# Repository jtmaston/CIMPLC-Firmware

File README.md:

<div style="text-align: justify">

# CIMPLC 
The CIMPLC is a low-cost, open source high pin-count programmable logic controller, designed as a project while studying at the University of Politehnica, Bucharest. It is designed as a replacement for the aging hardware found inside the CIM ( Computer Integrated Manufacturing ) workcell located in our faculty.

# The software
The firmware is based on FreeRTOS, offering vast functionality. The stand-out feature of this design is the implementation of the concept of vPLC, or virtual PLC. It also implements a fast optimizing compiler to translate IEC 61131-3 instructions to bytecode which can be loaded faster from EEPROM.

Fast, predictible code execution is the goal of every system, and the CIMPLC is no exception. The end-goal of the code is to be implemented according to the most rigorous standards. In its final version, code will be written following the MISRA standard.
## Features [WIP]

### WiFi programmability and monitoring
The software allows both firmware updates over the air (OTA), as well as binary uploads for the PLC.

Furthermore, the status of the PLC can be monitored at any time by the use of a web interface. Pin status, direction, and code execution can be accessed, as well as whatever logs may be produced by the code.

### vPLC
vPLC, short for Virtual PLC, simplifies the concept of a PLC to its simplest form: a finite state machine. This allows for the creation of multiple threads of execution, each with access to I/Os and interfaces, while having distinct memory spaces, program stacks and counters. This allows for higher flexibility of the system.

### WASM
## Limitations

???
## Contributors

Mihai Costin, for the WASM magic [@mihaicostin34](https://github.com/mihaicostin34)
## License

This project is licensed under [GNU AGPLv3](https://choosealicense.com/licenses/agpl-3.0/).
</div>

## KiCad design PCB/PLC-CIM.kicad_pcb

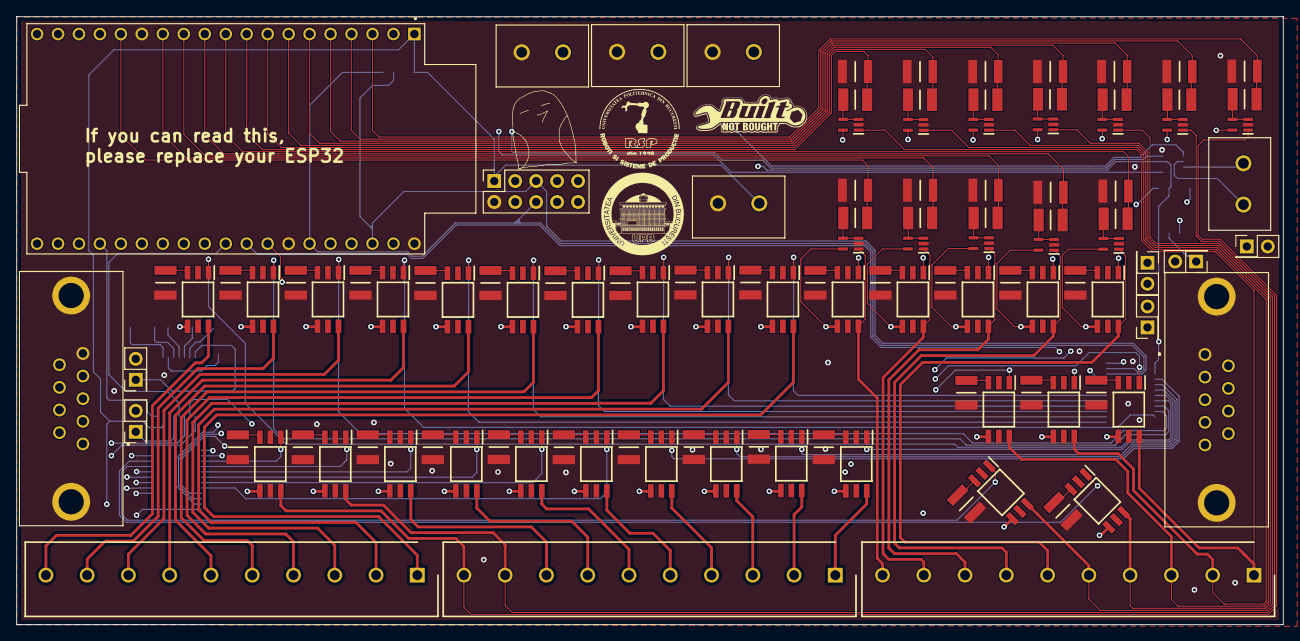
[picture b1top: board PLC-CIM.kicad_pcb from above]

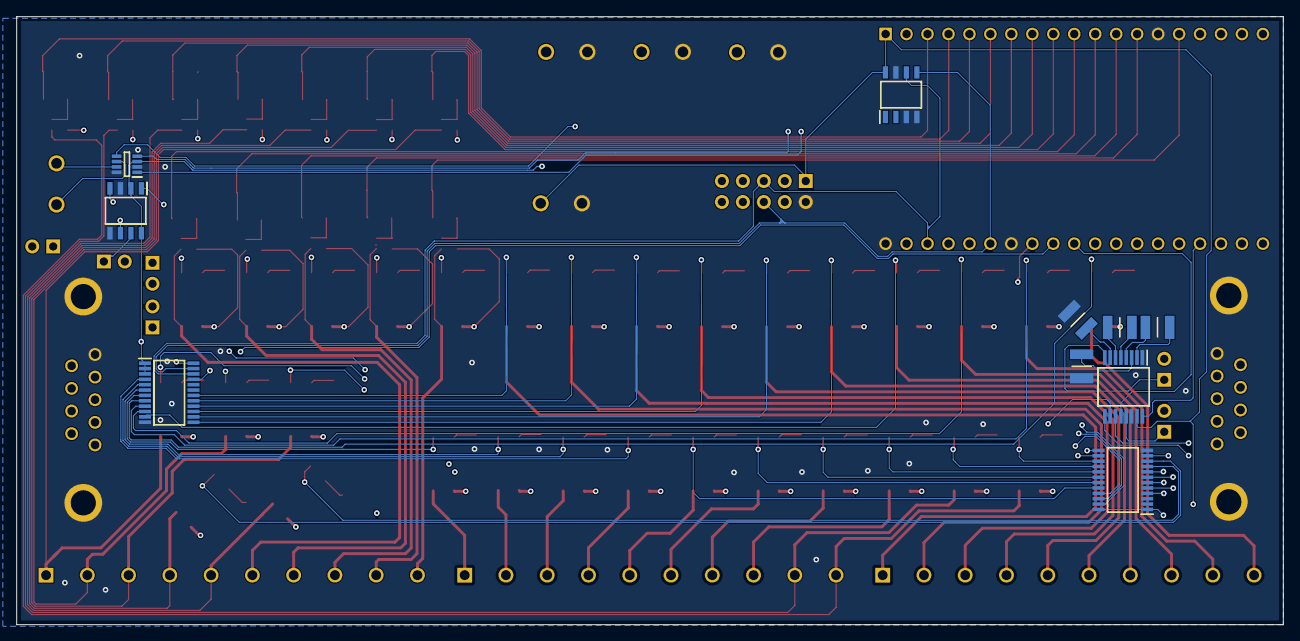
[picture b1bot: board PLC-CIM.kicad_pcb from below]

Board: 4 copper layers, 153.5 x 73.7 mm, 124 parts (10 on the bottom side), 149 nets.

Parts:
C1, C2, C3, C4: 12103C104KAT2A; CAPC3325X94N
IC1, IC2, IC3, IC4, IC5, IC6, IC13, IC14, IC15, IC16, IC17, IC18, IC25, IC26, IC27, IC28, IC29, IC30, IC32, IC33, IC34, IC35, IC36, IC37, IC38, IC39, IC40, IC41, IC42, IC43: TLP172AM_TPR,E; SOIC127P700X230-6N
IC7, IC8, IC9, IC10, IC11, IC12, IC19, IC20, IC21, IC22, IC23, IC24: TLV9351IDCKR; SOT65P210X110-5N
IC31: MAX3221IDBRE4; SOP65P780X200-16N
IC44, IC46: PCA9555PW,118; SOP65P640X110-24N
IC45: TCAN337DCNR; SOT65P280X145-8N
IC47: SN65HVD75DR; SOIC127P600X175-8N
J1, J2, J3: TB001-500-10BE; SHDR10W100P0X500_1X10_5000X900X1250P
J4, J5, J6, J7, J12: TC0203620000G
J8, J13: 750678-1; 7506781
J9, J10, J14, J15, J16, J17: Conn_02x01; PinHeader_2x01_P2.54mm_Vertical
J11: Conn_02x05_Odd_Even; PinSocket_2x05_P2.54mm_Vertical
R1, R2, R3, R4, R5, R6, R19, R20, R21, R22, R23, R24, R37, R38, R39, R40, R41, R42, R43, R44, R45, R46, R47, R48, R49, R50, R51, R52, R53, R54: CRCW1210267RFKEA; RESC3225X60N
R7, R8, R9, R10, R11, R12, R25, R26, R27, R28, R29, R30: RK73B2ETTD152J; RESC3226X70N
R13, R14, R15, R16, R17, R18, R31, R32, R33, R34, R35, R36: RMCF1210FT10K0; RESC3225X70N
U1: ESP32-DEVKITC; MODULE_ESP32-DEVKITC
U2: AT24CM02-SSHM-B; SOIC127P600X175-8N

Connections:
+3.3V: IC31.15 (VCC), IC44.1 (~INT), IC44.2 (A1), IC44.3 (A2), IC44.24 (VDD), IC45.3 (VCC), IC46.1 (~INT), IC46.2 (A1), IC46.3 (A2), IC46.24 (VDD), IC47.2 (~RE), IC47.8 (VCC), J5.1, J11.1, U1.1 (3V3), U2.8 (VCC)
+24V: IC1.4 (DRAIN_1), IC2.4 (DRAIN_1), IC3.4 (DRAIN_1), IC4.4 (DRAIN_1), IC5.4 (DRAIN_1), IC6.4 (DRAIN_1), IC7.5 (V+), IC8.5 (V+), IC9.5 (V+), IC10.5 (V+), IC11.5 (V+), IC12.5 (V+), IC13.4 (DRAIN_1), IC14.4 (DRAIN_1), IC15.4 (DRAIN_1), IC16.4 (DRAIN_1), IC17.4 (DRAIN_1), IC18.4 (DRAIN_1), IC19.5 (V+), IC20.5 (V+), IC21.5 (V+), IC22.5 (V+), IC23.5 (V+), IC24.5 (V+), IC25.4 (DRAIN_1), IC26.4 (DRAIN_1), IC27.4 (DRAIN_1), IC28.4 (DRAIN_1), IC29.4 (DRAIN_1), IC30.4 (DRAIN_1), IC32.4 (DRAIN_1), IC33.4 (DRAIN_1), IC34.4 (DRAIN_1), IC35.4 (DRAIN_1), IC36.4 (DRAIN_1), IC37.4 (DRAIN_1), IC38.4 (DRAIN_1), IC39.4 (DRAIN_1), IC40.4 (DRAIN_1), IC41.4 (DRAIN_1), IC42.4 (DRAIN_1), IC43.4 (DRAIN_1), J4.1, J6.1, J7.1, J17.2
/O Block 1/O_ACT_1: IC6.1 (ANODE), IC44.4 (I/O0_0)
/O Block 1/O_ACT_2: IC5.1 (ANODE), IC44.5 (I/O0_1)
/O Block 1/O_ACT_3: IC4.1 (ANODE), IC44.6 (I/O0_2)
/O Block 1/O_ACT_4: IC3.1 (ANODE), IC44.7 (I/O0_3)
/O Block 1/O_ACT_5: IC2.1 (ANODE), IC44.8 (I/O0_4)
/O Block 1/O_ACT_6: IC1.1 (ANODE), IC44.9 (I/O0_5)
/O Block 2/O_ACT_1: IC18.1 (ANODE), IC44.10 (I/O0_6)
/O Block 2/O_ACT_2: IC17.1 (ANODE), IC44.11 (I/O0_7)
/O Block 2/O_ACT_3: IC16.1 (ANODE), IC44.13 (I/O1_0)
/O Block 2/O_ACT_4: IC15.1 (ANODE), IC44.14 (I/O1_1)
/O Block 2/O_ACT_5: IC14.1 (ANODE), IC44.15 (I/O1_2)
/O Block 2/O_ACT_6: IC13.1 (ANODE), IC44.16 (I/O1_3)
/O Block 3/O_ACT_1: IC30.1 (ANODE), IC44.17 (I/O1_4)
/O Block 3/O_ACT_2: IC29.1 (ANODE), IC44.18 (I/O1_5)
/O Block 3/O_ACT_3: IC28.1 (ANODE), IC44.19 (I/O1_6)
/O Block 3/O_ACT_4: IC27.1 (ANODE), IC44.20 (I/O1_7)
/O Block 3/O_ACT_5: IC26.1 (ANODE), IC46.4 (I/O0_0)
/O Block 3/O_ACT_6: IC25.1 (ANODE), IC46.5 (I/O0_1)
/O Block 4/O_ACT_1: IC37.1 (ANODE), IC46.6 (I/O0_2)
/O Block 4/O_ACT_2: IC36.1 (ANODE), IC46.7 (I/O0_3)
/O Block 4/O_ACT_3: IC35.1 (ANODE), IC46.8 (I/O0_4)
/O Block 4/O_ACT_4: IC34.1 (ANODE), IC46.9 (I/O0_5)
/O Block 4/O_ACT_5: IC33.1 (ANODE), IC46.10 (I/O0_6)
/O Block 4/O_ACT_6: IC32.1 (ANODE), IC46.11 (I/O0_7)
/O Block 5/O_ACT_1: IC43.1 (ANODE), IC46.13 (I/O1_0)
/O Block 5/O_ACT_2: IC42.1 (ANODE), IC46.14 (I/O1_1)
/O Block 5/O_ACT_3: IC41.1 (ANODE), IC46.15 (I/O1_2)
/O Block 5/O_ACT_4: IC40.1 (ANODE), IC46.16 (I/O1_3)
/O Block 5/O_ACT_5: IC39.1 (ANODE), IC46.17 (I/O1_4)
/O Block 5/O_ACT_6: IC38.1 (ANODE), IC46.18 (I/O1_5)
ADR_1: IC44.21 (A0), U1.31 (IO19)
ADR_2: IC46.21 (A0), U1.30 (IO18)
CAN_FAULT: IC45.5 (FAULT), U1.26 (IO4)
CAN_RX: IC45.1 (TXD), U1.24 (IO2)
CAN_TX: IC45.4 (RXD), U1.25 (IO0)
FORCEOFF: IC31.12 (FORCEON), U1.29 (IO5)
FORCEON: IC31.16 (~FORCEOFF), U1.23 (IO15)
GND: C3.1, C4.2, IC7.2 (V-), IC8.2 (V-), IC9.2 (V-), IC10.2 (V-), IC11.2 (V-), IC12.2 (V-), IC19.2 (V-), IC20.2 (V-), IC21.2 (V-), IC22.2 (V-), IC23.2 (V-), IC24.2 (V-), IC31.1 (~EN), IC31.14 (GND), IC44.12 (VSS), IC45.2 (GND), IC45.8 (S), IC46.12 (VSS), IC47.3 (DE), IC47.5 (GND), J4.2, J5.2, J6.2, J7.2, J8.5, J8.MH1, J8.MH2, J11.2, J13.1, J13.MH1, J13.MH2, R1.2, R2.2, R3.2, R4.2, R5.2, R6.2, R7.2, R8.2, R9.2, R10.2, R11.2, R12.2, R19.2, R20.2, R21.2, R22.2, R23.2, R24.2, R25.2, R26.2, R27.2, R28.2, R29.2, R30.2, R37.2, R38.2, R39.2, R40.2, R41.2, R42.2, R43.2, R44.2, R45.2, R46.2, R47.2, R48.2, R49.2, R50.2, R51.2, R52.2, R53.2, R54.2, U1.14 (GND1), U1.32 (GND2), U1.38 (GND3), U2.3 (A2), U2.4 (GND), U2.7 (WP)
GPIO_1: IC6.6 (DRAIN_2), IC8.1 (IN+), J1.10
GPIO_2: IC5.6 (DRAIN_2), IC7.1 (IN+), J1.9
GPIO_3: IC4.6 (DRAIN_2), IC12.1 (IN+), J1.8
GPIO_4: IC3.6 (DRAIN_2), IC11.1 (IN+), J1.7
GPIO_5: IC2.6 (DRAIN_2), IC10.1 (IN+), J1.6
GPIO_6: IC1.6 (DRAIN_2), IC9.1 (IN+), J1.5
GPIO_7: IC18.6 (DRAIN_2), IC20.1 (IN+), J1.4
GPIO_8: IC17.6 (DRAIN_2), IC19.1 (IN+), J1.3
GPIO_9: IC16.6 (DRAIN_2), IC24.1 (IN+), J1.2
GPIO_10: IC15.6 (DRAIN_2), IC23.1 (IN+), J1.1
GPIO_11: IC14.6 (DRAIN_2), IC22.1 (IN+), J2.10
GPIO_12: IC13.6 (DRAIN_2), IC21.1 (IN+), J2.9
MCU_IN_1: R27.1, R33.2, U1.4 (SENSOR_VN)
MCU_IN_2: R28.1, R34.2, U1.3 (SENSOR_VP)
MCU_IN_3: R29.1, R35.2, U1.9 (IO25)
MCU_IN_4: R30.1, R36.2, U1.8 (IO33)
MCU_IN_5: R25.1, R31.2, U1.7 (IO32)
MCU_IN_6: R26.1, R32.2, U1.6 (IO35)
MCU_IN_7: R9.1, R15.2, U1.5 (IO34)
MCU_IN_8: R10.1, R16.2, U1.10 (IO26)
MCU_IN_9: R11.1, R17.2, U1.11 (IO27)
MCU_IN_10: R12.1, R18.2, U1.12 (IO14)
MCU_IN_11: R7.1, R13.2, U1.13 (IO12)
MCU_IN_12: R8.1, R14.2, U1.15 (IO13)
unnamed: IC1.3 (CATHODE), R1.1
unnamed: IC2.3 (CATHODE), R2.1
unnamed: IC3.3 (CATHODE), R3.1
unnamed: IC4.3 (CATHODE), R4.1
unnamed: IC5.3 (CATHODE), R5.1
unnamed: IC6.3 (CATHODE), R6.1
unnamed: IC7.3 (IN-), IC7.4 (OUT), R13.1
unnamed: IC8.3 (IN-), IC8.4 (OUT), R14.1
unnamed: IC9.3 (IN-), IC9.4 (OUT), R15.1
unnamed: IC10.3 (IN-), IC10.4 (OUT), R16.1
unnamed: IC11.3 (IN-), IC11.4 (OUT), R17.1
unnamed: IC12.3 (IN-), IC12.4 (OUT), R18.1
unnamed: IC13.3 (CATHODE), R19.1
unnamed: IC14.3 (CATHODE), R20.1
unnamed: IC15.3 (CATHODE), R21.1
unnamed: IC16.3 (CATHODE), R22.1
unnamed: IC17.3 (CATHODE), R23.1
unnamed: IC18.3 (CATHODE), R24.1
unnamed: IC19.3 (IN-), IC19.4 (OUT), R31.1
unnamed: IC20.3 (IN-), IC20.4 (OUT), R32.1
unnamed: IC21.3 (IN-), IC21.4 (OUT), R33.1
unnamed: IC22.3 (IN-), IC22.4 (OUT), R34.1
unnamed: IC23.3 (IN-), IC23.4 (OUT), R35.1
unnamed: IC24.3 (IN-), IC24.4 (OUT), R36.1
unnamed: IC25.3 (CATHODE), R37.1
unnamed: IC26.3 (CATHODE), R38.1
unnamed: IC27.3 (CATHODE), R39.1
unnamed: IC28.3 (CATHODE), R40.1
unnamed: IC29.3 (CATHODE), R41.1
unnamed: IC30.3 (CATHODE), R42.1
unnamed: C1.2, IC31.2 (C1+)
unnamed: C1.1, IC31.4 (C1-)
unnamed: C2.2, IC31.5 (C2+)
unnamed: C2.1, IC31.6 (C2-)
unnamed: IC31.13 (DOUT), J9.1
unnamed: IC31.8 (RIN), J10.1
unnamed: C3.2, IC31.3 (V+)
unnamed: C4.1, IC31.7 (V-)
unnamed: IC32.3 (CATHODE), R43.1
unnamed: IC33.3 (CATHODE), R44.1
unnamed: IC34.3 (CATHODE), R45.1
unnamed: IC35.3 (CATHODE), R46.1
unnamed: IC36.3 (CATHODE), R47.1
unnamed: IC37.3 (CATHODE), R48.1
unnamed: IC38.3 (CATHODE), R49.1
unnamed: IC39.3 (CATHODE), R50.1
unnamed: IC40.3 (CATHODE), R51.1
unnamed: IC41.3 (CATHODE), R52.1
unnamed: IC42.3 (CATHODE), R53.1
unnamed: IC43.3 (CATHODE), R54.1
unnamed: IC45.7 (CANH), J12.2
unnamed: IC45.6 (CANL), J12.1
unnamed: IC47.6 (A), J15.1
unnamed: IC47.7 (B), J14.1
unnamed: J8.2, J9.2
unnamed: J8.3, J10.2
unnamed: J13.3, J14.2
unnamed: J13.8, J15.2
unnamed: J13.6, J16.1
unnamed: J13.7, J17.1
OUT_13: IC30.6 (DRAIN_2), J2.8
OUT_14: IC29.6 (DRAIN_2), J2.7
OUT_15: IC28.6 (DRAIN_2), J2.6
OUT_16: IC27.6 (DRAIN_2), J2.5
OUT_17: IC26.6 (DRAIN_2), J2.4
OUT_18: IC25.6 (DRAIN_2), J2.3
OUT_19: IC37.6 (DRAIN_2), J2.2
OUT_20: IC36.6 (DRAIN_2), J2.1
OUT_21: IC35.6 (DRAIN_2), J3.10
OUT_22: IC34.6 (DRAIN_2), J3.9
OUT_23: IC33.6 (DRAIN_2), J3.8
OUT_24: IC32.6 (DRAIN_2), J3.7
OUT_25: IC43.6 (DRAIN_2), J3.6
OUT_26: IC42.6 (DRAIN_2), J3.5
OUT_27: IC41.6 (DRAIN_2), J3.4
OUT_28: IC40.6 (DRAIN_2), J3.3
OUT_29: IC39.6 (DRAIN_2), J3.2
OUT_30: IC38.6 (DRAIN_2), J3.1
RS232_STATUS: IC31.10 (~INVALID), U1.37 (IO23)
RX0: IC31.9 (ROUT), U1.34 (RXD0)
RX1: IC47.1 (R), U1.27 (IO16)
SCL: IC44.22 (SCL), IC46.22 (SCL), J11.5, U1.36 (IO22), U2.6 (SCL)
SDA: IC44.23 (SDA), IC46.23 (SDA), J11.6, U1.33 (IO21), U2.5 (SDA)
TX0: IC31.11 (DIN), U1.35 (TXD0)
TX1: IC47.4 (D), U1.28 (IO17)

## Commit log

2023-04-22 Remove some garbage
2023-04-22 # Title: Summary, imperative, start upper case, don't end with a period # No more than 50 chars. #### 50 chars is here: # Prepping repo
    # Remember blank line between title and body.
    # Body: Explain *what* and *why* (not *how*). Include task ID (Jira issue).
    # Wrap at 72 chars. ################################## which is here: #
    Deleted lib files that did not belong to KiCAD
    Altered project paths to be referenced to local project, ensuring portability
    # At the end: Include Co-authored-by for all contributors.
2023-04-22 Revert "# Title: Summary, imperative, start upper case, don't end with a period"
    This reverts commit 68e2e82ae65b044d3f55e91a7adcee939c25789e.
2023-04-22 Revert "Revert "# Title: Summary, imperative, start upper case, don't end with a period""
    This reverts commit 3a20dd9da141c7cb1bae8077342d3450242b15f5.
2023-04-23 Finalized generalized design
2023-04-23 Redesigned, to utilize the ESP32 as the basis
    * Implemented EEPROM
    * Implemented RTC
    * Implemented RS232 and 485
    * Implemented CANBus
    * Implemented everything
2023-04-23 Implemented Output block in PCB Started implementation of Input block in PCB
2023-04-25 Finalized PCB
2023-05-02 augh
2023-05-06 Add partition tables
2023-05-06 Add launch ink
2023-05-06 Add shortcut to open vscode with esp
2023-05-08 Added improvements towards bootloader stub size
2023-05-08 remove artefacts
2023-05-08 What the fudge happened to the repo
2023-05-10 Finalized partitioning
2023-05-10 Actually set partitions right
2023-05-14 Completed bootloaderStub, with full(tm) functionality * Un-minified the HTML * Disabled all prints * Disabled NVS * Added some additional error checking * Increased the chunk size, but discovered tha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
2023-05-14 Fixed a bug that caused incorrect uploads
2023-05-14 Added Powershell script as export target
2023-05-14 Automated creation of both firmware and recovery firmware
2023-05-22 Cleaned up repo * Removed most legacy functions that would not be used * Removed confusing http module * Removed OTA reboot checking, since only one OTA partition will be used * Moved reboot counters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
2023-05-22 Very early eeprom support
2023-05-22 Bugfixes * Fixed some remnants of eeprom support
2023-05-22 no worky :(
2023-06-09 Worky :)
    * Implemented eeprom functionality
2023-06-09 Add eeprom submodule
2023-06-10 Remove hardware from the repo
2023-06-11 Update license and readme
2023-06-11 Remove old sdkconfig files
2023-06-11 Re-add all eeprom sources from old repo
2023-06-11 Build.yml
2023-06-11 Update partition map
2023-06-11 Add workflow and partitionMap
2023-06-11 Add status badge
2023-06-11 Re-add eeprom
2023-06-16 fix loading wasm program
2023-06-18 Add driver submodule - Update submodules - Removed some .old files
2023-06-18 Set submodules to track master
2023-06-18 Start work - Update eeprom module - Create files
2023-06-18 corrected submodule
2023-06-29 WIP WIP WIP
2023-06-29 http err
2023-10-05 Update ioCtrl driver
2023-10-05 Re-built the IO controller, and tested all outputs
